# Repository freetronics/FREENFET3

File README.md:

Freetronics FreeNFET Addressable 3x N-MOSFET Module
====================================================
Copyright 2016 Freetronics Pty Ltd  
Freetronics site:  www.freetronics.com  
Freetronics email: info@freetronics.com  

These are FETs with a brain! Includes 3 x NTD5867NL N-channel MOSFETs and
a WS2811 addressable LED driver. That means you can connect the module
and address it just as if it was a NeoPixel or other WS28xx RGB LED, 
except that instead of controlling an LED, you're controlling 3 high-power
MOSFETs.

This smart module can be daisy-chained, so you can connect a number of
these together in a string and drive each of them individually from your
microcontroller.

Compatible with various Arduino libraries for the WS2811, including
the FastLED library and the NeoPixel library. Simply control the "red",
"green", and "blue" channels to control the FETs.

Features:

 * Switch up to 60V / 18A DC per FET.
 * Requires just 1 data connection.
 * PWM control of the FETs.
 * Input and output headers on opposite sides of the board for easy
   daisy-chaining.

More information is available at:

  http://www.freetronics.com.au/freenfet3

INSTALLATION
------------
The design is saved as an EAGLE project. EAGLE PCB design software is
available from www.cadsoftusa.com free for non-commercial use. To use
this project download it and place the directory containing these files
into the "eagle" directory on your computer.

DISTRIBUTION
------------
The specific terms of distribution of this project are governed by the
license referenced below.

LICENSE
-------
Licensed under the TAPR Open Hardware License (www.tapr.org/OHL).
The "license" folder within this repository also contains a copy of
this license in plain text format.

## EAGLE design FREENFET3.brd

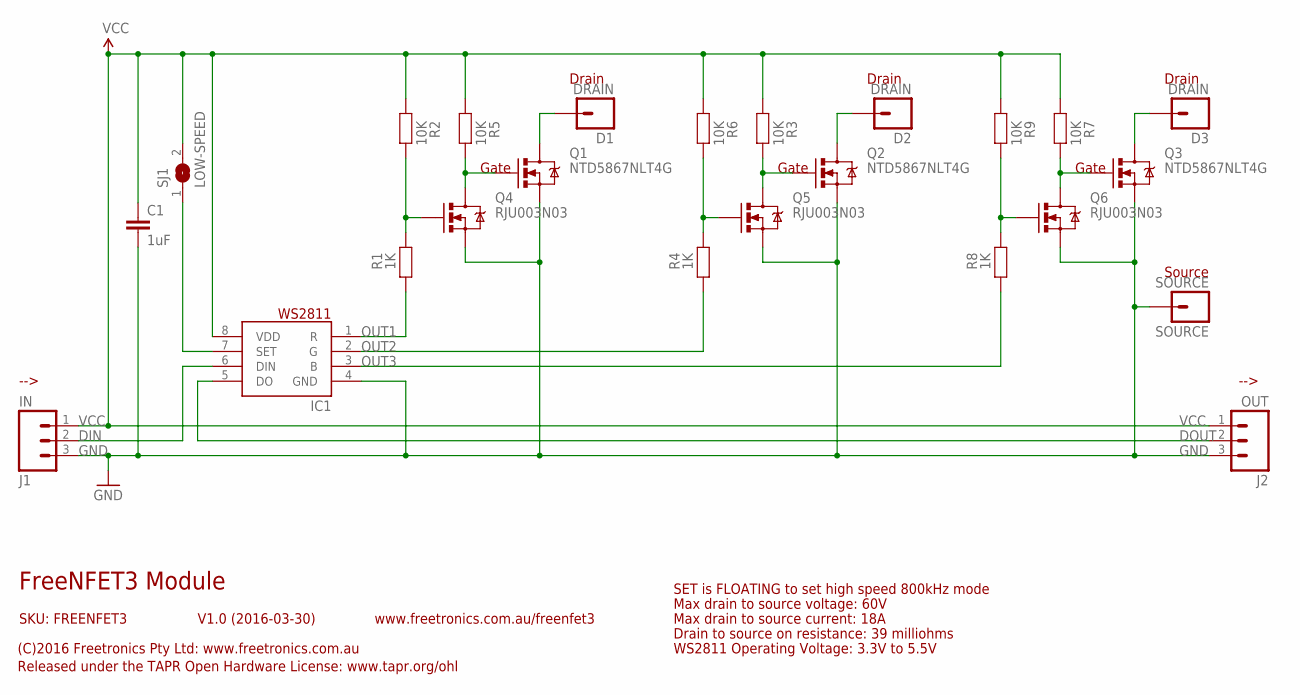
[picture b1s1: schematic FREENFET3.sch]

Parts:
C1: 1uF; 0603
D1, D2, D3: DRAIN; 1X01LARGE
IC1: WS2811-SOP8; SO08-SKINNYPADS
J1: IN; 1X03
J2: OUT; 1X03
Q1, Q2, Q3: NTD5867NLT4G; DPACK
Q4, Q5, Q6: RJU003N03; SOT32-3
R1, R4, R8: 1K; 0603
R2, R3, R5, R6, R7, R9: 10K; 0603
SJ1: LOW-SPEED; SJ
SOURCE: SOURCE; 1X01LARGE

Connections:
D: D1.1, Q1.2 (D)
D1: D2.1, Q2.2 (D)
D2: D3.1, Q3.2 (D)
DIN: IC1.6 (DIN), J1.2
DOUT: IC1.5 (DO), J2.2
GND: C1.2, IC1.4 (GND), J1.3, J2.3, Q1.3 (S), Q2.3 (S), Q3.3 (S), Q4.2 (S), Q5.2 (S), Q6.2 (S), SOURCE.1
unnamed: Q2.1 (G), Q5.3 (D), R3.1
unnamed: Q4.1 (G), R1.1, R2.1
unnamed: Q1.1 (G), Q4.3 (D), R5.1
unnamed: Q5.1 (G), R4.1, R6.1
unnamed: Q3.1 (G), Q6.3 (D), R7.1
unnamed: Q6.1 (G), R8.1, R9.1
unnamed: IC1.7 (SET), SJ1.1
OUT1: IC1.1 (R), R1.2
OUT2: IC1.2 (G), R4.2
OUT3: IC1.3 (B), R8.2
VCC: C1.1, IC1.8 (VDD), J1.1, J2.1, R2.2, R3.2, R5.2, R6.2, R7.2, R9.2, SJ1.2

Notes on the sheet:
FreeNFET3 Module
V1.0 (2016-03-30)
SKU: FREENFET3
(C)2016 Freetronics Pty Ltd: www.freetronics.com.au
Released under the TAPR Open Hardware License: www.tapr.org/ohl
www.freetronics.com.au/freenfet3
WS2811 Operating Voltage: 3.3V to 5.5V
-->
SET is FLOATING to set high speed 800kHz mode
Max drain to source current: 18A
Drain
Gate
Source
Max drain to source voltage: 60V
Drain to source on resistance: 39 milliohms

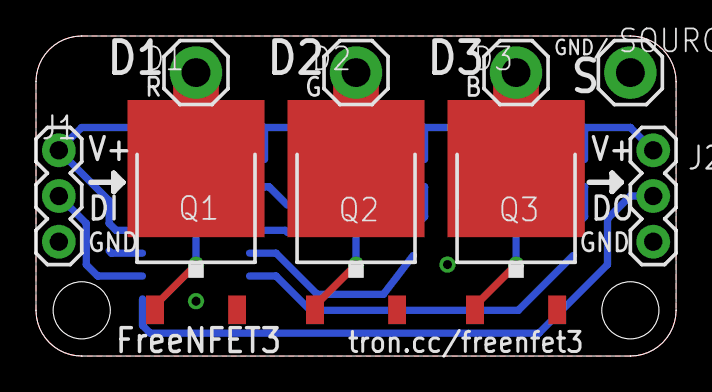
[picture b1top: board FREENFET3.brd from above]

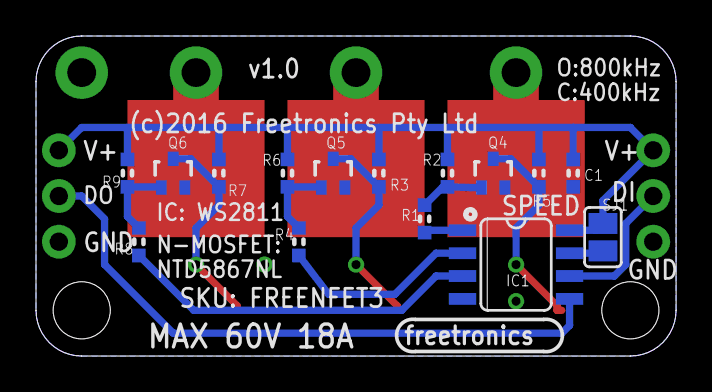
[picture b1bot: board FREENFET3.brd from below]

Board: 2 copper layers, 35.6 x 17.8 mm, 24 parts (15 on the bottom side), 17 nets.

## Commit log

2016-09-26 Initial import
2019-04-23 Final layout
